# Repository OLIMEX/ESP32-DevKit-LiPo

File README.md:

# ESP32-DevKit-LiPo
Open Source Hardware OSHW ESP32 development board designed with KiCAD to be pin to pin compatible with Espressif ESP32-DevKitC, but with additional LiPo charger and battery

## License
* Hardware is released under Apache 2.0 License
* Software is released under GPL3 License
* Documentation is released under CC BY-SA 3.0

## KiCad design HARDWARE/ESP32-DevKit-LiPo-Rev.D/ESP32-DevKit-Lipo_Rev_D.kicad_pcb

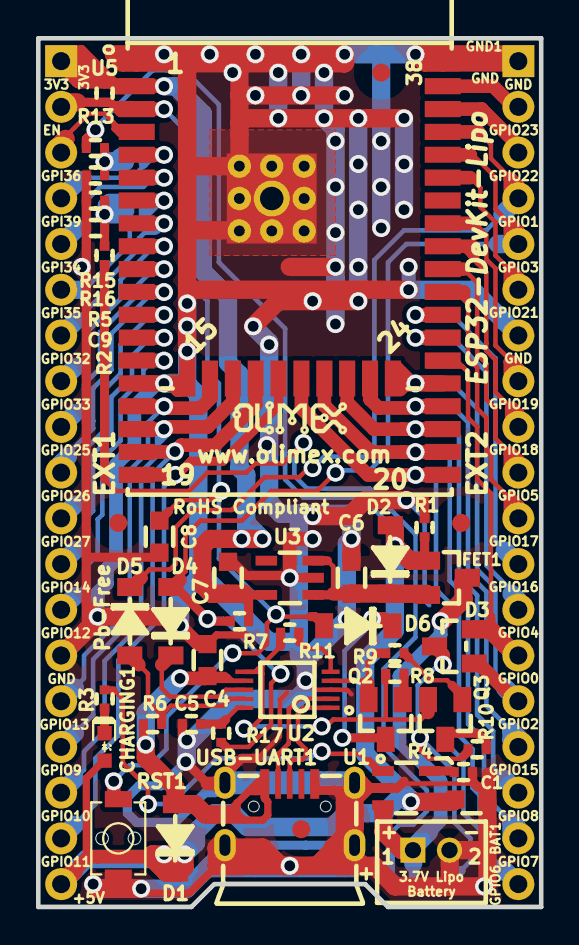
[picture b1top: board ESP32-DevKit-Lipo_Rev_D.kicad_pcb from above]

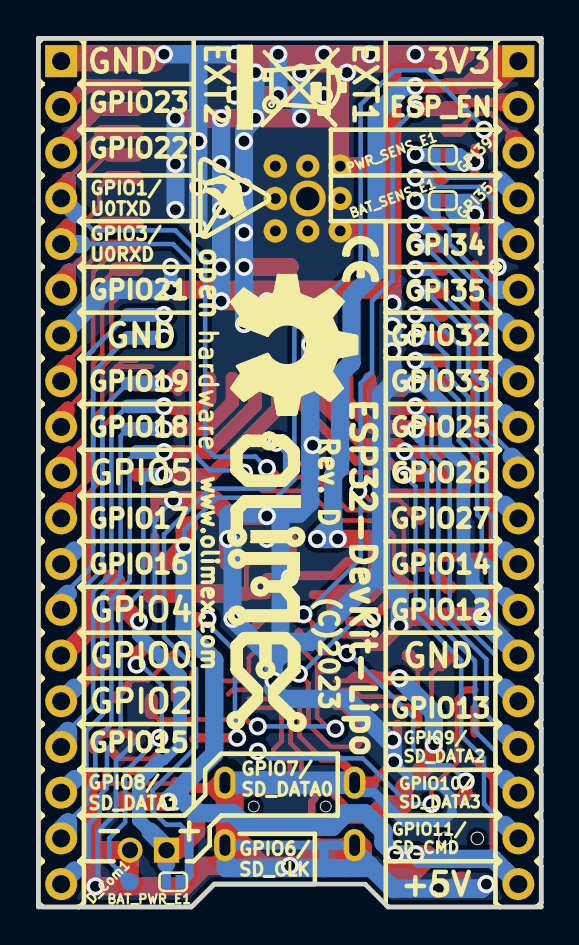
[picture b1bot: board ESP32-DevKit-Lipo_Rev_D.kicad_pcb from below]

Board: 2 copper layers, 27.9 x 48.3 mm, 56 parts (11 on the bottom side), 58 nets.

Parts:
BAT1: DW02S; LIPO_BAT_VERTICAL_DW02S
BAT_PWR_E1: Opened; SJ_1_SMALLER
BAT_SENS_E1: Opened; SJ_1_SMALLER
C1, C4: 22uF/6.3V/20%/X5R/C0603; C_0603_5MIL_DWS
C5, C9: 100nF/10V/10%/X7R/C0402; C_0402_5MIL_DWS
C6, C7: 4.7uF/6.3V/C0603; C_0603_5MIL_DWS
C8: 1uF/10V/10%/X5R/C0603; C_0603_5MIL_DWS
CHARGING1: LED/YELLOW/0603; LED_0603_KA
D1, D2, D4, D5, D6: 1N5819S4/SOD123; SOD-123_1C-2A_KA
D3: BAT54C(SOT23-3); SOT23-3
D_Com1: TESTPAD; TESTPAD_40-ROUND
EXT1, EXT2: HN1x19
FET1: WPM2015-3/TR; SOT23
FID1: Fiducial; Fiducial1x3_Past
FID2, FID3, FID4: Fiducial; Fiducial1x3
GND1: TESTPAD; TESTPAD_40-ROUND
Logo_OSHW: LOGO_OPENHARDWARE_8x8
Olimex_Logo_Big: OLIMEX_LOGO_TB
Olimex_Logo_Small: LOGO_OLIMEX_80
PWR_SENS_E1: Opened; SJ_1_SMALLER
Q2, Q3: BC817-40(SOT23); SOT23
R1, R6, R13, R17: 10k/R0402; R_0402_5MIL_DWS
R2, R5, R16: 470k/R0402; R_0402_5MIL_DWS
R3, R4, R8, R9: 2.2k/R0402; R_0402_5MIL_DWS
R7: NA/R0402; R_0402_5MIL_DWS
R10: 220R/R0402; R_0402_5MIL_DWS
R11: 4.7k/R0402; R_0402_5MIL_DWS
R15: 220k/R0402; R_0402_5MIL_DWS
RST1: IT-1185AU2-160G-G-TR; IT1185AU2_V2
Sign_Antistatic: Val**; LOGO_ANTISTATIC_SMALL_4.5mmX2.8mm
Sign_CE_Small: CE_Sign_Small
Sign_RecycleBin: LOGO_RECYCLEBIN_1
U1: BL4054B-42TPRN(SOT23-5); SOT-23-5
U2: CH340X(MSOP-10); MSOP-10_Pitch-0.5mm_3.00x3.00x1.00mm
U3: HX6211A332MR; SOT-23-5
U5: ESP32-WROOM-32D-4MB; ESP32-WROVER_MODULE
USB-UART1: MISB-SWMM-5B-LF(USB_MICRO); USB-MICRO_MISB-SWMM-5B_LF

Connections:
+3.3V: C7.1, EXT1.1, R7.2, R13.1, U3.5, U5.2
+5V: C1.1, CHARGING1.2, D1.1, D2.2, EXT1.19, FET1.1, R1.1, R15.1, U1.4
/+5V_USB: C4.1, D1.2, R6.1, U2.7, USB-UART1.1
/D_Com: D3.3, D_Com1.1, R10.2
/ESP_EN: C8.1, D6.2, EXT1.2, R13.2, RST1.1, U5.3
/GPI34: EXT1.5, U5.6
/GPI35: BAT_SENS_E1.2, EXT1.6, U5.7
/GPI36\SENSOR_VP: EXT1.3, U5.4
/GPI39\SENSOR_VN: EXT1.4, PWR_SENS_E1.2, U5.5
/GPIO0: D3.2, EXT2.14, U5.25
/GPIO1\U0TXD: D5.1, EXT2.4, U5.35
/GPIO2: D3.1, EXT2.15, U5.24
/GPIO3\U0RXD: D4.2, EXT2.5, R7.1, R17.2, U5.34
/GPIO4: EXT2.13, U5.26
/GPIO5: EXT2.10, U5.29
/GPIO6\SD_CLK: EXT2.19, U5.20
/GPIO7\SD_DATA0: EXT2.18, U5.21
/GPIO8\SD_DATA1: EXT2.17, U5.22
/GPIO9\SD_DATA2: EXT1.16, U5.17
/GPIO10\SD_DATA3: EXT1.17, U5.18
/GPIO11\SD_CMD: EXT1.18, U5.19
/GPIO12: EXT1.13, U5.14
/GPIO13: EXT1.15, U5.16
/GPIO14: EXT1.12, U5.13
/GPIO15: EXT2.16, U5.23
/GPIO16: EXT2.12, U5.27
/GPIO17: EXT2.11, U5.28
/GPIO18: EXT2.9, U5.30
/GPIO19: EXT2.8, U5.31
/GPIO21: EXT2.6, U5.33
/GPIO22: EXT2.3, U5.36
/GPIO23: EXT2.2, U5.37
/GPIO25: EXT1.9, U5.10
/GPIO26: EXT1.10, U5.11
/GPIO27: EXT1.11, U5.12
/GPIO32: EXT1.7, U5.8
/GPIO33: EXT1.8, U5.9
GND: BAT1.2, C1.2, C4.2, C5.2, C6.2, C7.2, C8.2, C9.1, EXT1.14, EXT2.1, EXT2.7, GND1.1, R1.2, R4.2, R5.2, R16.2, RST1.2, U1.2, U2.3, U3.2, U5.1, U5.15, U5.38, U5.39, USB-UART1.0, USB-UART1.5
unnamed: BAT_PWR_E1.1, R2.1
unnamed: BAT_SENS_E1.1, C9.2, R2.2, R5.1
unnamed: C5.1, R17.1, U2.10
unnamed: C6.1, D2.1, FET1.2, U3.1, U3.3
unnamed: CHARGING1.1, R3.1
unnamed: D4.1, U2.8
unnamed: D5.2, R6.2, U2.9
unnamed: D6.1, Q2.3
unnamed: PWR_SENS_E1.1, R15.2, R16.1
unnamed: Q2.1, R8.2
unnamed: Q2.2, R9.1, U2.4
unnamed: Q3.1, R9.2
unnamed: Q3.2, R8.1, R11.1, U2.6
unnamed: Q3.3, R10.1
unnamed: R3.2, U1.1
unnamed: R4.1, U1.5
unnamed: R11.2, U2.5
unnamed: U2.1, USB-UART1.3
unnamed: U2.2, USB-UART1.2
VBAT: BAT1.1, BAT_PWR_E1.2, FET1.3, U1.3

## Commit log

2018-09-27 initial Rev.A1
2020-06-08 Update
    Revision B
2020-07-28 Update
    Hardware revision C files
2024-09-19 Updated
    Added revision D files
2024-12-04 Update
    Added manual
2025-06-17 Update
    Added photos

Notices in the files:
HARDWARE/ESP32-DevKit-LiPo-Rev.D/ESP32-DevKit-Lipo_Rev_D.kicad_pcb:
(C)2023
